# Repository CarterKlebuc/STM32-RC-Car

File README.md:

# STM32-RC-Car
RC Car powered by a STM32 Microcontroller which accepts commands from a MATLAB App via Bluetooth

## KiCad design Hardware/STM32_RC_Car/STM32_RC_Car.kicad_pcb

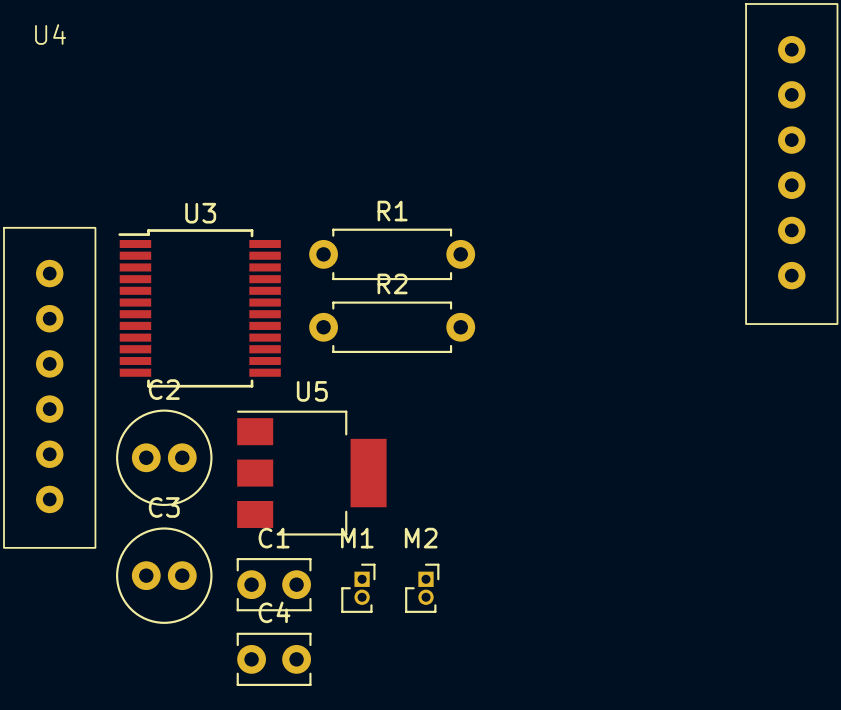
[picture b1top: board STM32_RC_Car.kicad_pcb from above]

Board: 2 copper layers, 11 parts (0 on the bottom side), 8 nets, no tracks yet.

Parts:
C1, C4: 0.1uF; C_Disc_D3.8mm_W2.6mm_P2.50mm
C2, C3: 10uF; C_Radial_D5.0mm_H11.0mm_P2.00mm
M1, M2: Motor_DC; PinSocket_1x02_P1.00mm_Vertical
R1, R2: R10K; R_Axial_DIN0207_L6.3mm_D2.5mm_P7.62mm_Horizontal
U3: TB6612FNG; SSOP-24_5.3x8.2mm_P0.65mm
U4: HC-05_Bluetooth_Custom
U5: LD1117S33TR_SOT223; SOT-223-3_TabPin2

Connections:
+3V3: C3.1, C4.1, U3.20 (VCC)
+9V: C1.1, C2.1, U3.13 (VM2), U3.14 (VM3), U3.24 (VM1), U5.3 (VI)
GND: C1.2, C2.2, C3.2, C4.2, R2.2, U3.3 (PGND1), U3.4 (PGND1), U3.9 (PGND2), U3.10 (PGND2), U3.18 (GND), U4.1 (KEY), U4.3 (GND), U4.6 (STATE), U5.1 (GND)
unnamed: M1.1 (+), U3.1 (AO1), U3.2 (AO1)
unnamed: M1.2 (-), U3.5 (AO2), U3.6 (AO2)
unnamed: M2.1 (+), U3.11 (BO1), U3.12 (BO1)
unnamed: M2.2 (-), U3.7 (BO2), U3.8 (BO2)
unnamed: R1.2, R2.1
